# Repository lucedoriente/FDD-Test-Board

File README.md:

# Retro-Diag FDD Master Tester & Exerciser

**Autore / Hardware Designer**: Alessio Iodice (<alessio67@gmail.com>)  
**Serie Hardware**: Retro-Diag Diagnostic Instruments  
**Revisione Hardware**: `1.0` (`2026-11-02` — Validazione KiCad 9.0)  
**Licenza**: CC BY-NC-SA 4.0  

---

## 1. Panoramica del Progetto

Il **Retro-Diag FDD Master Tester & Exerciser** è uno strumento da banco universale ad alte prestazioni per il collaudo, la riparazione, la taratura meccanica e l'allineamento delle testine di qualsiasi unità floppy disk prodotta tra il 1971 e la fine degli anni '90.

L'hardware è progettato con standard di laboratorio:
* **Copertura Totale dei Formati**:
  - **Drive 8 Pollici**: Shugart SA800/801, SA850/851, Siemens FDD100-8D, Memorex 651, PerSci, sistemi S-100/CP/M (soft-sector e hard-sector a 32 fori).
  - **Drive 5.25 Pollici**: Standard Shugart SA400/450 (35 tracce), PC/XT/AT (40 e 80 tracce: 160K, 180K, 320K, 360K, 720K Quad, 1.2M High Density a 360 RPM).
  - **Drive 3.5 Pollici**: 720 KB (Double Density), 1.44 MB (High Density), 2.88 MB (Extended Density a 1 Mbps e registrazione perpendicolare), varianti Apple/Amiga/Apricot.
  - **Drive 3 Pollici "Compact Floppy"**: Amstrad CPC 664/6128, Amstrad PCW 8256/8512, Sinclair ZX Spectrum +3, Tatung Einstein.
  - **Drive Apple II e Meccaniche Nude**: Apple II Disk II (20 pin) e connettore diretto a 4 fasi per motori stepper a magnete permanente (Commodore 1541).

---

## 2. Architettura Meccanica ed Ergonomia

Per garantire massima comodità di montaggio, dissipazione termica passiva e cablaggio ordinato, la scheda adotta le seguenti specifiche:
* **Dimensioni PCB**: **$200.0 \times 140.0\text{ mm}$** (PCB a 4 strati ad alta immunità ai disturbi, stackup JLCPCB JLC04161H-7628 con piani GND e Power dedicati).
* **Bordo Posteriore (Connettori a 90° angolari per cavi standard)**:
  - `J_FDD50`: Maschio IDC 50 pin a 90° (cavo piatto standard drive 8").
  - `J_FDD34`: Maschio IDC 34 pin a 90° polarizzato (cavo piatto standard 5.25" e 3.5").
  - `J_FDD26`: Maschio IDC 26 pin a 90° (cavo piatto 3" Amstrad/Spectrum e HP).
  - `J_APPLE20`: Maschio IDC 20 pin a 90° (cavo nastro Apple II Disk II).
  - `J_PWR_525`: Connettore Molex 4 pin maschio a 90° (+12V, GND, GND, +5V).
  - `J_PWR_350`: Connettore Berg floppy 4 pin maschio a 90° (+5V, GND, GND, +12V).
  - `J_PWR_800`: Morsettiera Phoenix passo 5.08 mm a 90° (+24V, +5V, GND, -12V/-5V).
  - `J_IN_24V`: Ingresso morsettiera a 90° dai 24V del modulo Mean Well interno.
* **Bordo Sinistro (Interfaccia PC)**:
  - Presa **USB Type-C** montata a filo con chip di protezione ESD `USBLC6-2SC6` per telemetria, dump dei dati e aggiornamento firmware.
* **Pannello Superiore / Frontale (Interfaccia Utente & Strumentazione)**:
  - Display grafico IPS a colori da **2.8" / 3.2"** (320 × 240 pixel, controller SPI ST7789V).
  - **Daughterboard Pannello Frontale (`FDD_UI_Panel`)**: Modulo dedicato da pannello ($120.0 \times 38.0\text{ mm}$, 2 layer) collegato alla scheda principale mediante cavo a nastro IDC polarizzato 14 poli (2×7 pitch 2.54 mm):
    - Encoder rotativo industriale Bourns PEC12R con pulsante integrato (`SELECT / PUSH`).
    - 3 Pulsanti tattili da pannello (`RUN`, `BACK`, `RESET`).
    - 5 Indicatori LED di stato ad alta visibilità (`READY`, `BUSY`, `FAULT`, `INDEX`, `READ`).
  - Basetta con **Punti di Test (Test Points)** con anelli di terra per sonde oscilloscopio 10x:
    `TP_GND`, `TP_INDEX`, `TP_READ_DATA`, `TP_TRACK0`, `TP_STEP`, `TP_DIR`, `TP_WRITE_GATE`.

---

## 3. Sezione di Alimentazione e Sicurezza Attiva (Zero-Smoke)

* **Alimentatore Integrato nel Case**: Modulo industriale **Mean Well IRM-60-24ST** o **EPS-65-24** (ingresso universale 90–264 VAC con vaschetta posteriore IEC C14 con fusibile e interruttore).
* **Rail di Potenza e Protezioni E-Fuse**:
  1. **+24V DC (fino a 2.5A)**: Diretto per motori ed elettromagnete di carico testina dei drive da 8".
  2. **+12V DC (fino a 2.5A)**: Convertitore Buck sincrono ad altissima efficienza (Texas Instruments `TPS54302`).
  3. **+5V DC (fino a 3.0A)**: Convertitore Buck sincrono ad altissima efficienza (Texas Instruments `TPS54302`).
  4. **-12V / -5V (fino a 50mA)**: Micro pompa di carica invertente (`TPS63700` o `LMC7660`) per bias comparatori vintage 8".
* **Misura Corrente e Trip di Protezione**:
  - Ogni rail (+24V, +12V, +5V) è dotato di shunt di precisione e amplificatore current-sense **INA180A1**.
  - Spegnimento istantaneo in $< 5\text{ }\mu\text{s}$ in caso di cortocircuito o motore bloccato, con allarme grafico a video.

---

## 4. Modalità Operative Firmware

1. **Wizard Guidato per Principianti**:
   - Riconoscimento assistito, schemi grafici a video di collegamento pin 1.
   - Test automatico a 5 passi: Check cortocircuiti $\to$ Sensori disco/WP $\to$ Misura precisa RPM ($\pm 0.1\text{ RPM}$) $\to$ Seek su tutte le tracce $\to$ Esito finale in italiano.
2. **Allineamento Testine (Analog Alignment Mode)**:
   - Cicli automatici tra Traccia 00, Traccia Centrale (16, 38 o 40) e Traccia Interna (39, 76, 79) per taratura lobo cat-eye e azimut con disco Dysan/Accurite.
3. **Generatore Pattern Read/Write & Flux**:
   - Generazione di pattern MFM/FM alle frequenze standard: 125 kHz, 250 kHz, 500 kHz e **1 MHz (ED 2.88MB)**.
   - Verifica di risposta del canale di preamplificazione e lettura del drive.

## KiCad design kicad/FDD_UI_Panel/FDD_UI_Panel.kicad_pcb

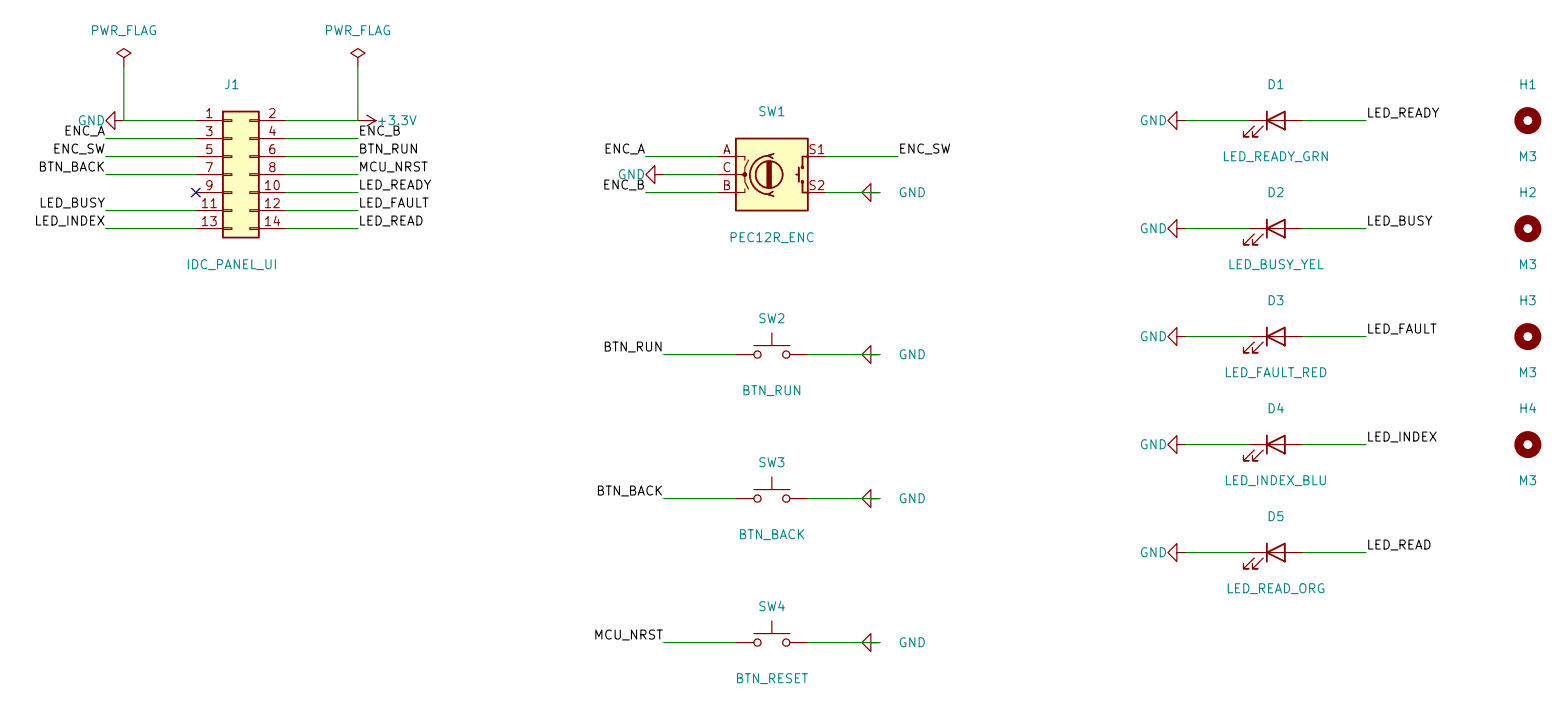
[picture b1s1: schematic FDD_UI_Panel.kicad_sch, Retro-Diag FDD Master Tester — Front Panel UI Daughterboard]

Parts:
D1: LED_READY_GRN; LED_D3.0mm
D2: LED_BUSY_YEL; LED_D3.0mm
D3: LED_FAULT_RED; LED_D3.0mm
D4: LED_INDEX_BLU; LED_D3.0mm
D5: LED_READ_ORG; LED_D3.0mm
H1, H2, H3, H4: M3; MountingHole_3.2mm_M3
J1: IDC_PANEL_UI; IDC-Header_2x07_P2.54mm_Vertical
SW1: PEC12R_ENC; RotaryEncoder_Bourns_Vertical_PEC12R-3x17F-Sxxxx
SW2: BTN_RUN; SW_PUSH_6mm_H5mm
SW3: BTN_BACK; SW_PUSH_6mm_H5mm
SW4: BTN_RESET; SW_PUSH_6mm_H5mm

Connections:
+3.3V: J1.2
/BTN_BACK: J1.7, SW3.1
/BTN_RUN: J1.6, SW2.1
/ENC_A: J1.3, SW1.A
/ENC_B: J1.4, SW1.B
/ENC_SW: J1.5, SW1.S1
/LED_BUSY: D2.2 (A), J1.11
/LED_FAULT: D3.2 (A), J1.12
/LED_INDEX: D4.2 (A), J1.13
/LED_READ: D5.2 (A), J1.14
/LED_READY: D1.2 (A), J1.10
/MCU_NRST: J1.8, SW4.1
GND: D1.1 (K), D2.1 (K), D3.1 (K), D4.1 (K), D5.1 (K), J1.1, SW1.C, SW1.S2, SW2.2, SW3.2, SW4.2

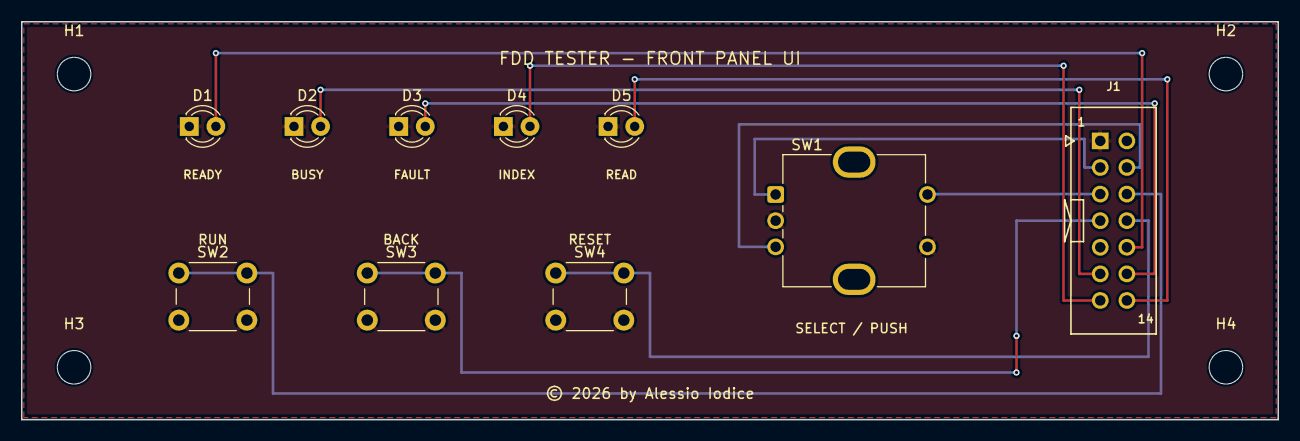
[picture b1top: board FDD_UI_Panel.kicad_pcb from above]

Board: 2 copper layers, 120.0 x 38.0 mm, 14 parts (0 on the bottom side), 12 nets.

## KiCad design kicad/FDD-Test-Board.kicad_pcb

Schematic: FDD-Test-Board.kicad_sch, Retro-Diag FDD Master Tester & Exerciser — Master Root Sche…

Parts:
H1, H2, H3, H4, H5, H6, H7: MountingHole_3.2mm_M3

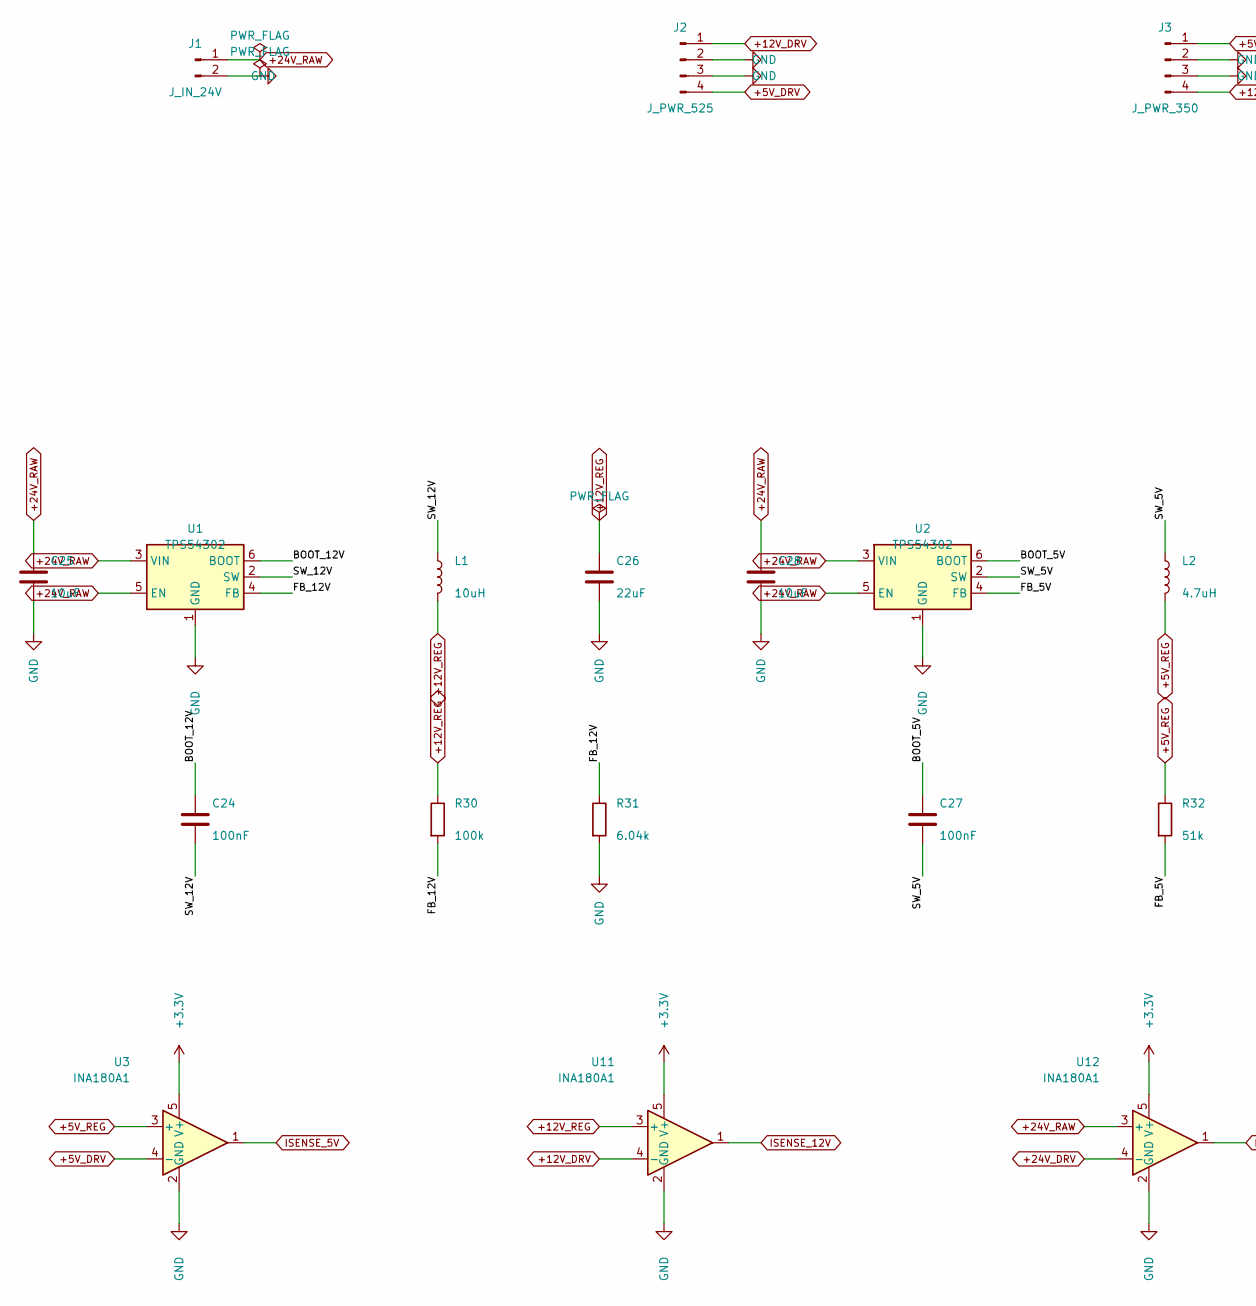
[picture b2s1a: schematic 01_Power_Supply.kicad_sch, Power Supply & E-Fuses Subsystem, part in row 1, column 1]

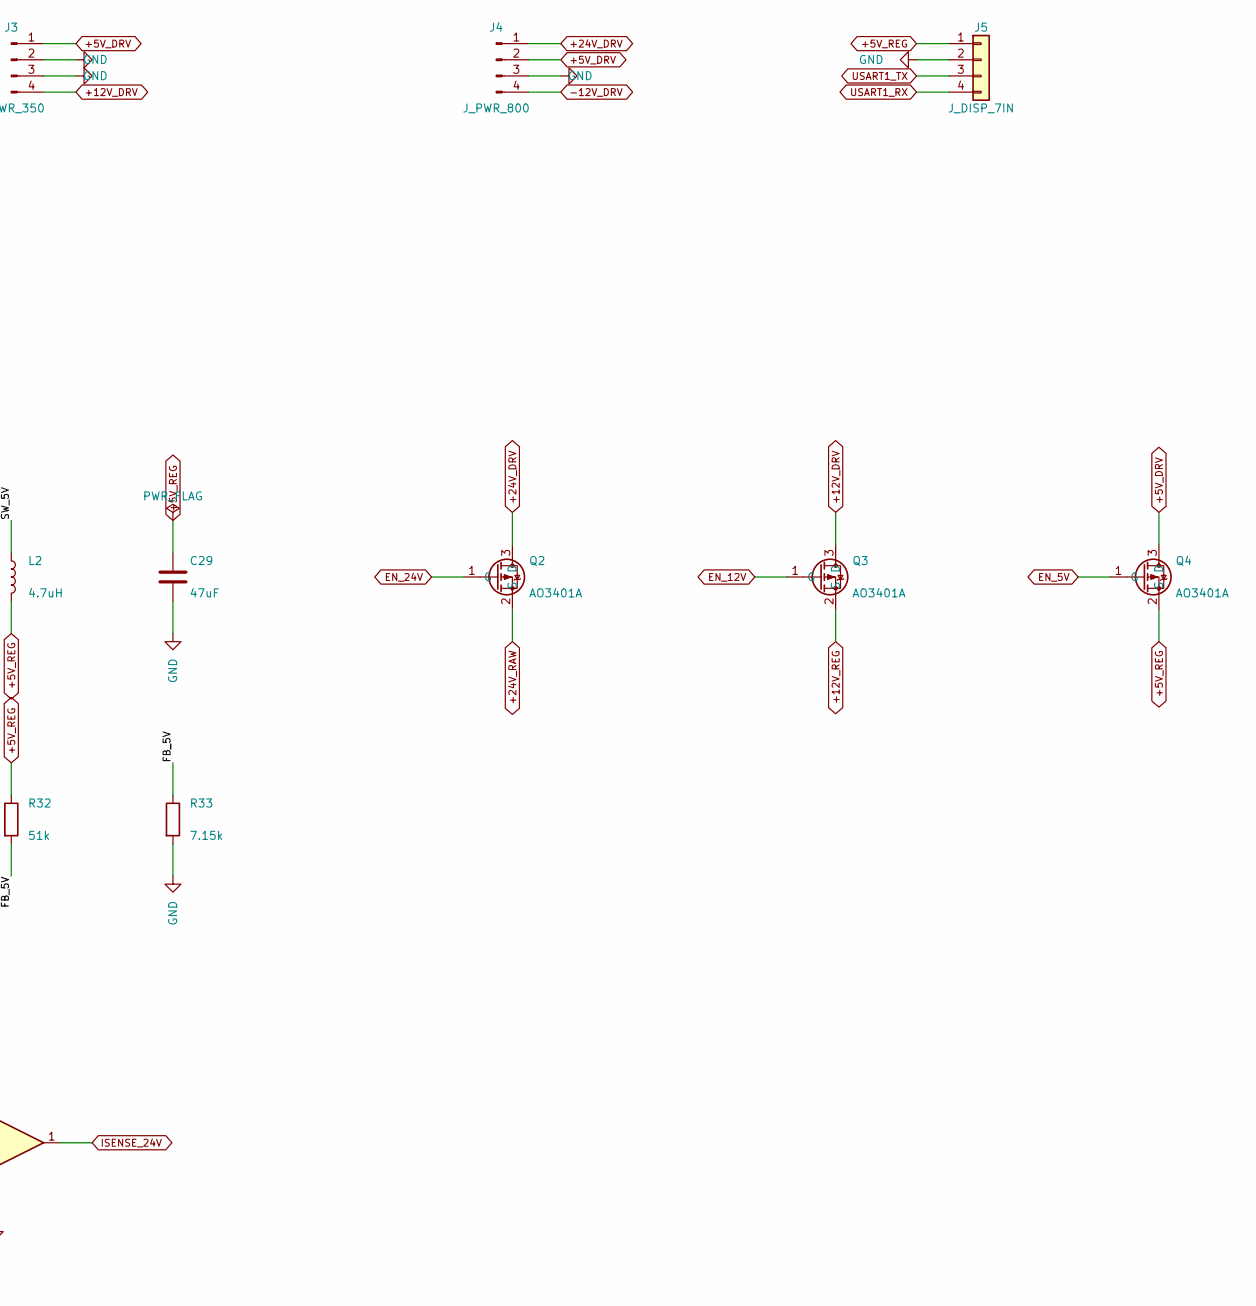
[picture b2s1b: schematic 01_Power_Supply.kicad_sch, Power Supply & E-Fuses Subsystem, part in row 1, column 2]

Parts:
C24, C27: 100nF; C_0805_2012Metric
C25, C28: 10uF; C_1210_3225Metric
C26: 22uF; C_1206_3216Metric
C29: 47uF; C_1206_3216Metric
J1: J_IN_24V; TerminalBlock_Phoenix_MKDS-1,5-2-5.08_1x02_P5.08mm_Horizont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
J2: J_PWR_525; TerminalBlock_Phoenix_MKDS-1,5-4-5.08_1x04_P5.08mm_Horizont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
J3: J_PWR_350; PinHeader_1x04_P2.54mm_Horizontal
J4: J_PWR_800; TerminalBlock_Phoenix_MKDS-1,5-4-5.08_1x04_P5.08mm_Horizont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
J5: J_DISP_7IN; PinHeader_1x04_P2.54mm_Vertical
L1: 10uH; L_7.3x7.3_H4.5
L2: 4.7uH; L_7.3x7.3_H4.5
Q2, Q3, Q4: AO3401A; SOT-23
R30: 100k; R_0805_2012Metric
R31: 6.04k; R_0805_2012Metric
R32: 51k; R_0805_2012Metric
R33: 7.15k; R_0805_2012Metric
U1, U2: TPS54302; SOT-23-6
U3, U11, U12: INA180A1; SOT-23-5

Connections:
+3.3V: U3.5 (V+), U11.5 (V+), U12.5 (V+); also elsewhere on the board
+5V_DRV: J2.4, J3.1, J4.2, Q4.3 (D), U3.4 (-); also elsewhere on the board
+5V_REG: C29.1, J5.1, L2.2, Q4.2 (S), R32.1, U3.3 (+); also elsewhere on the board
+12V_DRV: J2.1, J3.4, Q3.3 (D), U11.4 (-); also elsewhere on the board
+12V_REG: C26.1, L1.2, Q3.2 (S), R30.1, U11.3 (+)
+24V_DRV: J4.1, Q2.3 (D), U12.4 (-)
+24V_RAW: C25.1, C28.1, J1.1, Q2.2 (S), U1.3 (VIN), U1.5 (EN), U2.3 (VIN), U2.5 (EN), U12.3 (+)
-12V_DRV: J4.4; also elsewhere on the board
/Power_Supply/BOOT_5V: C27.1, U2.6 (BOOT)
/Power_Supply/BOOT_12V: C24.1, U1.6 (BOOT)
/Power_Supply/FB_5V: R32.2, R33.1, U2.4 (FB)
/Power_Supply/FB_12V: R30.2, R31.1, U1.4 (FB)
/Power_Supply/SW_5V: C27.2, L2.1, U2.2 (SW)
/Power_Supply/SW_12V: C24.2, L1.1, U1.2 (SW)
EN_5V: Q4.1 (G); also elsewhere on the board
EN_12V: Q3.1 (G); also elsewhere on the board
EN_24V: Q2.1 (G); also elsewhere on the board
GND: C25.2, C26.2, C28.2, C29.2, J1.2, J2.2, J2.3, J3.2, J3.3, J4.3, J5.2, R31.2, R33.2, U1.1 (GND), U2.1 (GND), U3.2 (GND), U11.2 (GND), U12.2 (GND); also elsewhere on the board
ISENSE_5V: U3.1; also elsewhere on the board
ISENSE_12V: U11.1; also elsewhere on the board
ISENSE_24V: U12.1; also elsewhere on the board
USART1_RX: J5.4; also elsewhere on the board
USART1_TX: J5.3; also elsewhere on the board

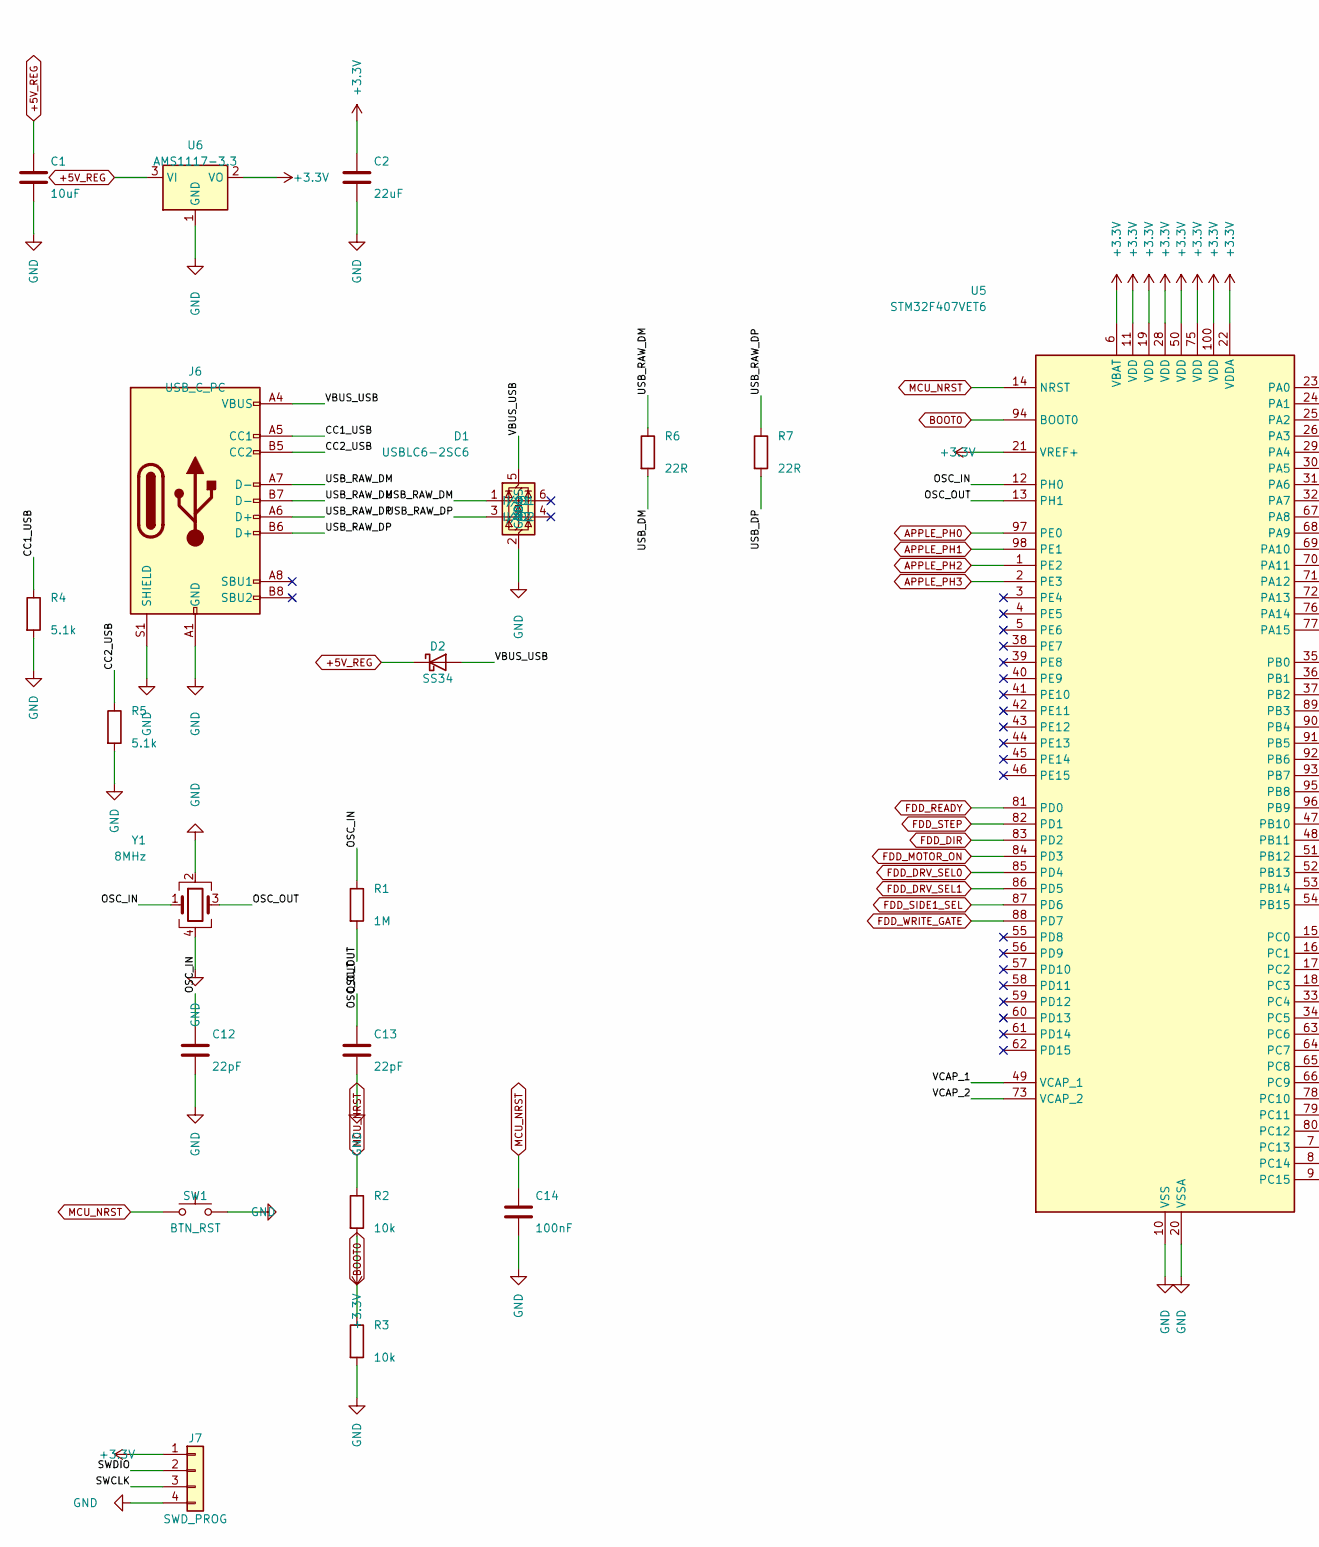
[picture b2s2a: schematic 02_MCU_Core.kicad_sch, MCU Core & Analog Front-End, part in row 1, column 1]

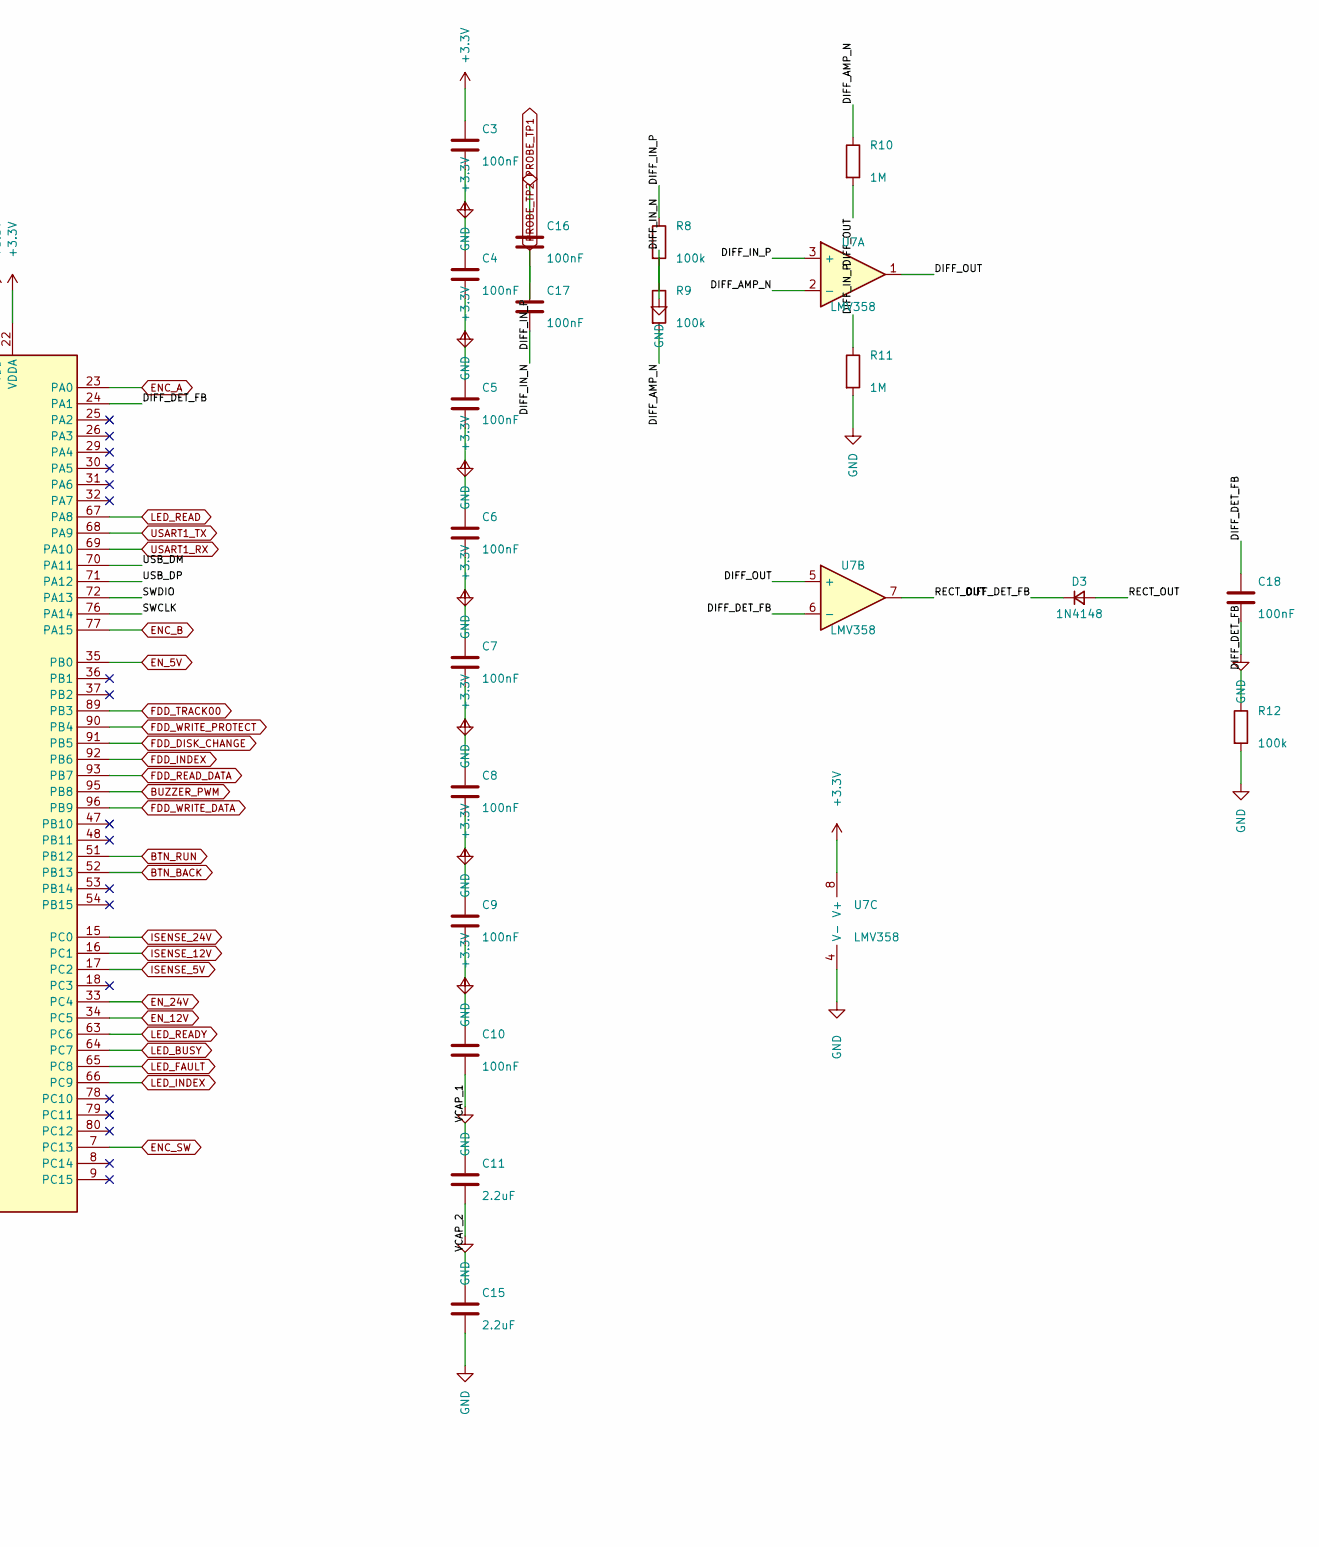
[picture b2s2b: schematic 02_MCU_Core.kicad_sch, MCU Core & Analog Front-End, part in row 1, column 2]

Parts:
C1: 10uF; C_0805_2012Metric
C2: 22uF; C_0805_2012Metric
C3, C4, C5, C6, C7, C8, C9, C10, C14, C16, C17, C18: 100nF; C_0805_2012Metric
C11, C15: 2.2uF; C_0805_2012Metric
C12, C13: 22pF; C_0805_2012Metric
D1: USBLC6-2SC6; SOT-23-6
D2: SS34; D_SMA
D3: 1N4148; D_SOD-123
J6: USB_C_PC; USB_C_Receptacle_HRO_TYPE-C-31-M-12
J7: SWD_PROG; PinHeader_1x04_P2.54mm_Vertical
R1, R10, R11: 1M; R_0805_2012Metric
R2, R3: 10k; R_0805_2012Metric
R4, R5: 5.1k; R_0805_2012Metric
R6, R7: 22R; R_0805_2012Metric
R8, R9, R12: 100k; R_0805_2012Metric
SW1: BTN_RST; SW_PUSH_6mm_H5mm
U5: STM32F407VET6; LQFP-100_14x14mm_P0.5mm
U6: AMS1117-3.3; SOT-223-3_TabPin2
U7: LMV358; SOIC-8_3.9x4.9mm_P1.27mm
Y1: 8MHz; Crystal_SMD_3225-4Pin_3.2x2.5mm

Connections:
+3.3V: C2.1, C3.1, C4.1, C5.1, C6.1, C7.1, C8.1, C9.1, C10.1, J7.1, R2.2, U5.6 (VBAT), U5.11 (VDD), U5.19 (VDD), U5.21 (VREF+), U5.22 (VDDA), U5.28 (VDD), U5.50 (VDD), U5.75 (VDD), U5.100 (VDD), U6.2 (VO), U7.8 (V+); also elsewhere on the board
+5V_REG: C1.1, D2.1 (K), U6.3 (VI); also elsewhere on the board
/MCU_Core/CC1_USB: J6.A5 (CC1), R4.1
/MCU_Core/CC2_USB: J6.B5 (CC2), R5.1
/MCU_Core/DIFF_AMP_N: R9.2, R10.1, U7.2 (-)
/MCU_Core/DIFF_DET_FB: C18.1, D3.1 (K), R12.1, U5.24 (PA1), U7.6 (-)
/MCU_Core/DIFF_IN_N: C17.2, R9.1
/MCU_Core/DIFF_IN_P: C16.2, R8.1, R11.1, U7.3 (+)
/MCU_Core/DIFF_OUT: R10.2, U7.1, U7.5 (+)
/MCU_Core/OSC_IN: C12.1, R1.1, U5.12 (PH0), Y1.1
/MCU_Core/OSC_OUT: C13.1, R1.2, U5.13 (PH1), Y1.3
/MCU_Core/RECT_OUT: D3.2 (A), U7.7
/MCU_Core/SWCLK: J7.3, U5.76 (PA14)
/MCU_Core/SWDIO: J7.2, U5.72 (PA13)
/MCU_Core/USB_DM: R6.2, U5.70 (PA11)
/MCU_Core/USB_DP: R7.2, U5.71 (PA12)
/MCU_Core/USB_RAW_DM: D1.1 (I/O1), J6.A7 (D-), J6.B7 (D-), R6.1
/MCU_Core/USB_RAW_DP: D1.3 (I/O2), J6.A6 (D+), J6.B6 (D+), R7.1
/MCU_Core/VBUS_USB: D1.5 (VBUS), D2.2 (A), J6.A4 (VBUS), J6.A9 (VBUS), J6.B4 (VBUS), J6.B9 (VBUS)
/MCU_Core/VCAP_1: C11.1, U5.49 (VCAP_1)
/MCU_Core/VCAP_2: C15.1, U5.73 (VCAP_2)
APPLE_PH0: U5.97 (PE0); also elsewhere on the board
APPLE_PH1: U5.98 (PE1); also elsewhere on the board
APPLE_PH2: U5.1 (PE2); also elsewhere on the board
APPLE_PH3: U5.2 (PE3); also elsewhere on the board
BOOT0: R3.1, U5.94 (BOOT0); also elsewhere on the board
BTN_BACK: U5.52 (PB13); also elsewhere on the board
BTN_RUN: U5.51 (PB12); also elsewhere on the board
BUZZER_PWM: U5.95 (PB8); also elsewhere on the board
ENC_A: U5.23 (PA0); also elsewhere on the board
ENC_B: U5.77 (PA15); also elsewhere on the board
ENC_SW: U5.7 (PC13); also elsewhere on the board
EN_5V: U5.35 (PB0); also elsewhere on the board
EN_12V: U5.34 (PC5); also elsewhere on the board
EN_24V: U5.33 (PC4); also elsewhere on the board
FDD_DIR: U5.83 (PD2); also elsewhere on the board
FDD_DISK_CHANGE: U5.91 (PB5); also elsewhere on the board
FDD_DRV_SEL0: U5.85 (PD4); also elsewhere on the board
FDD_DRV_SEL1: U5.86 (PD5); also elsewhere on the board
FDD_INDEX: U5.92 (PB6); also elsewhere on the board
FDD_MOTOR_ON: U5.84 (PD3); also elsewhere on the board
FDD_READY: U5.81 (PD0); also elsewhere on the board
FDD_READ_DATA: U5.93 (PB7); also elsewhere on the board
FDD_SIDE1_SEL: U5.87 (PD6); also elsewhere on the board
FDD_STEP: U5.82 (PD1); also elsewhere on the board
FDD_TRACK00: U5.89 (PB3); also elsewhere on the board
FDD_WRITE_DATA: U5.96 (PB9); also elsewhere on the board
FDD_WRITE_GATE: U5.88 (PD7); also elsewhere on the board
FDD_WRITE_PROTECT: U5.90 (PB4); also elsewhere on the board
GND: C1.2, C2.2, C3.2, C4.2, C5.2, C6.2, C7.2, C8.2, C9.2, C10.2, C11.2, C12.2, C13.2, C14.2, C15.2, C18.2, D1.2 (GND), J6.A1 (GND), J6.A12 (GND), J6.B1 (GND), J6.B12 (GND), J6.S1 (SHIELD), J7.4, R3.2, R4.2, R5.2, R8.2, R11.2, R12.2, SW1.2, U5.10 (VSS), U5.20 (VSSA), U5.27 (VSS), U5.74 (VSS), U5.99 (VSS), U6.1 (GND), U7.4 (V-), Y1.2, Y1.4; also elsewhere on the board
ISENSE_5V: U5.17 (PC2); also elsewhere on the board
ISENSE_12V: U5.16 (PC1); also elsewhere on the board
ISENSE_24V: U5.15 (PC0); also elsewhere on the board
LED_BUSY: U5.64 (PC7); also elsewhere on the board
LED_FAULT: U5.65 (PC8); also elsewhere on the board
LED_INDEX: U5.66 (PC9); also elsewhere on the board
LED_READ: U5.67 (PA8); also elsewhere on the board
LED_READY: U5.63 (PC6); also elsewhere on the board
MCU_NRST: C14.1, R2.1, SW1.1, U5.14 (NRST); also elsewhere on the board
PROBE_TP1: C16.1; also elsewhere on the board
PROBE_TP2: C17.1; also elsewhere on the board
USART1_RX: U5.69 (PA10); also elsewhere on the board
USART1_TX: U5.68 (PA9); also elsewhere on the board

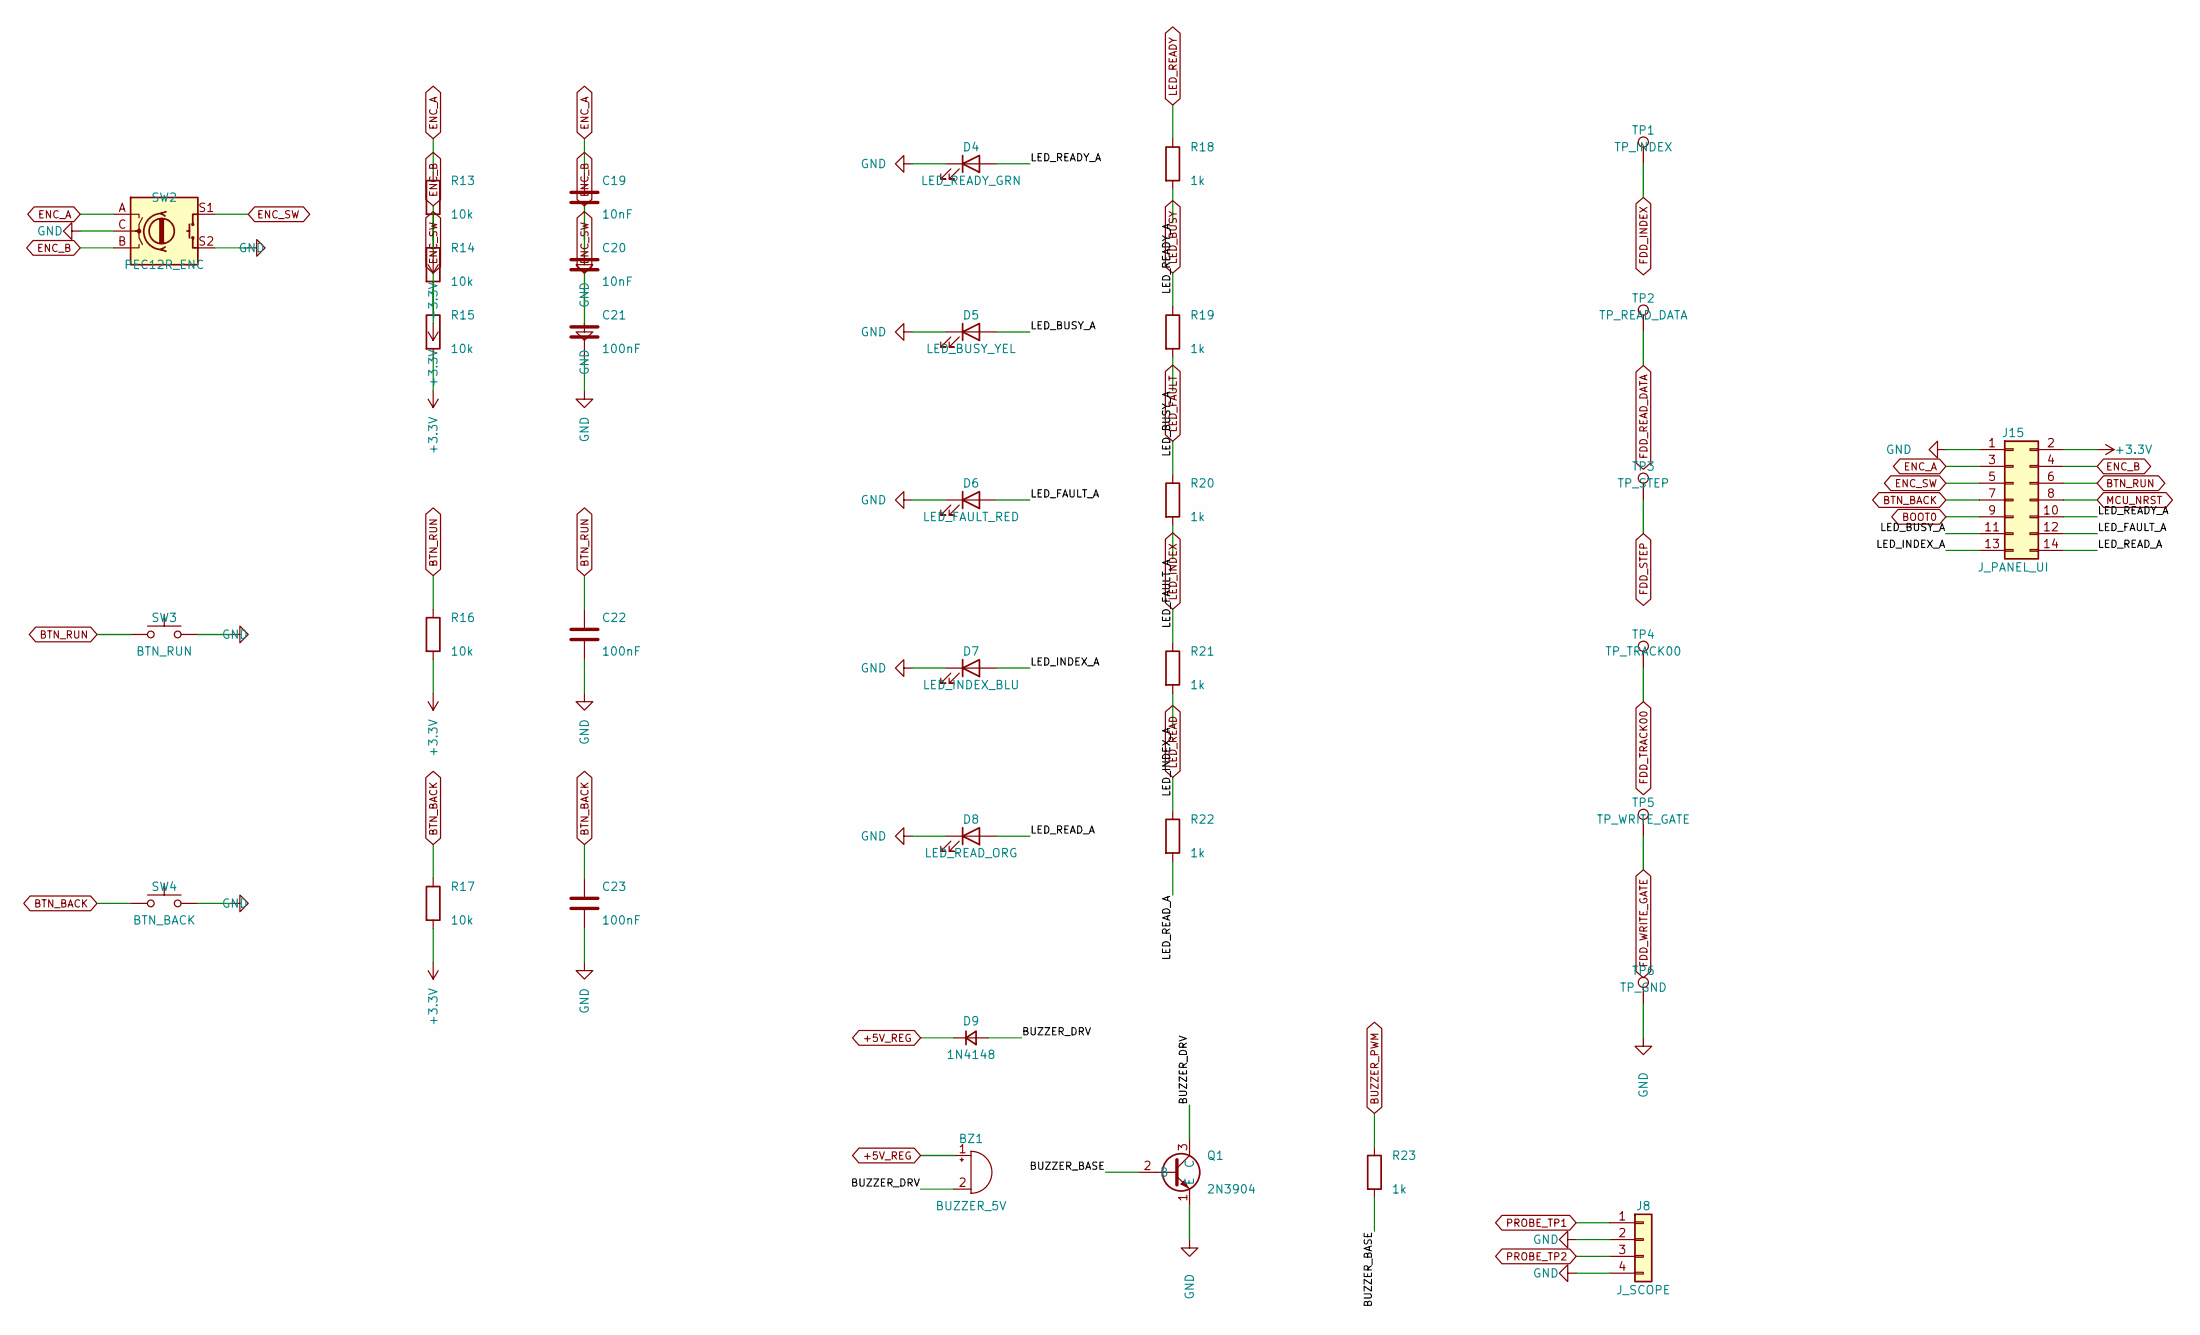
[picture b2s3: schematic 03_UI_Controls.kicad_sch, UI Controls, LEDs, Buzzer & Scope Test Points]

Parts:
BZ1: BUZZER_5V; Buzzer_12x9.5RM7.6
C19, C20: 10nF; C_0805_2012Metric
C21, C22, C23: 100nF; C_0805_2012Metric
D4: LED_READY_GRN; LED_0805_2012Metric
D5: LED_BUSY_YEL; LED_0805_2012Metric
D6: LED_FAULT_RED; LED_0805_2012Metric
D7: LED_INDEX_BLU; LED_0805_2012Metric
D8: LED_READ_ORG; LED_0805_2012Metric
D9: 1N4148; D_SOD-123
J8: J_SCOPE; PinHeader_1x04_P2.54mm_Vertical
J15: J_PANEL_UI; IDC-Header_2x07_P2.54mm_Vertical
Q1: 2N3904; SOT-23
R13, R14, R15, R16, R17: 10k; R_0805_2012Metric
R18, R19, R20, R21, R22, R23: 1k; R_0805_2012Metric
SW2: PEC12R_ENC; RotaryEncoder_Bourns_Vertical_PEC12R-3x17F-Sxxxx
SW3: BTN_RUN; SW_PUSH_6mm_H5mm
SW4: BTN_BACK; SW_PUSH_6mm_H5mm
TP1: TP_INDEX; TestPoint_Pad_D2.0mm
TP2: TP_READ_DATA; TestPoint_Pad_D2.0mm
TP3: TP_STEP; TestPoint_Pad_D2.0mm
TP4: TP_TRACK00; TestPoint_Pad_D2.0mm
TP5: TP_WRITE_GATE; TestPoint_Pad_D2.0mm
TP6: TP_GND; TestPoint_Pad_D2.0mm

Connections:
+3.3V: J15.2, R13.2, R14.2, R15.2, R16.2, R17.2; also elsewhere on the board
+5V_REG: BZ1.1 (+), D9.1 (K); also elsewhere on the board
/UI_Controls/BUZZER_BASE: Q1.2 (B), R23.2
/UI_Controls/BUZZER_DRV: BZ1.2 (-), D9.2 (A), Q1.3 (C)
/UI_Controls/LED_BUSY_A: D5.2 (A), J15.11, R19.2
/UI_Controls/LED_FAULT_A: D6.2 (A), J15.12, R20.2
/UI_Controls/LED_INDEX_A: D7.2 (A), J15.13, R21.2
/UI_Controls/LED_READY_A: D4.2 (A), J15.10, R18.2
/UI_Controls/LED_READ_A: D8.2 (A), J15.14, R22.2
BOOT0: J15.9; also elsewhere on the board
BTN_BACK: C23.1, J15.7, R17.1, SW4.1; also elsewhere on the board
BTN_RUN: C22.1, J15.6, R16.1, SW3.1; also elsewhere on the board
BUZZER_PWM: R23.1; also elsewhere on the board
ENC_A: C19.1, J15.3, R13.1, SW2.A; also elsewhere on the board
ENC_B: C20.1, J15.4, R14.1, SW2.B; also elsewhere on the board
ENC_SW: C21.1, J15.5, R15.1, SW2.S1; also elsewhere on the board
FDD_INDEX: TP1.1; also elsewhere on the board
FDD_READ_DATA: TP2.1; also elsewhere on the board
FDD_STEP: TP3.1; also elsewhere on the board
FDD_TRACK00: TP4.1; also elsewhere on the board
FDD_WRITE_GATE: TP5.1; also elsewhere on the board
GND: C19.2, C20.2, C21.2, C22.2, C23.2, D4.1 (K), D5.1 (K), D6.1 (K), D7.1 (K), D8.1 (K), J8.2, J8.4, J15.1, Q1.1 (E), SW2.C, SW2.S2, SW3.2, SW4.2, TP6.1; also elsewhere on the board
LED_BUSY: R19.1; also elsewhere on the board
LED_FAULT: R20.1; also elsewhere on the board
LED_INDEX: R21.1; also elsewhere on the board
LED_READ: R22.1; also elsewhere on the board
LED_READY: R18.1; also elsewhere on the board
MCU_NRST: J15.8; also elsewhere on the board
PROBE_TP1: J8.1; also elsewhere on the board
PROBE_TP2: J8.3; also elsewhere on the board

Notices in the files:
firmware/Inc/bsp_fdd_pins.h:
@license CC BY-NC-SA 4.0
kicad/FDD-Test-Board.kicad_pcb:
© 2026 by Alessio Iodice
